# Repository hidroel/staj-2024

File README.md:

# Proje Başlığı: Dizel Motor Su Pompası Ek Modülü

## 1. Giriş
### 1.1 Proje Tanımı
Müşterimiz, tarım sulama sisteminde kullandığı dizel motor su pompası ile ilgili bir sorun yaşamaktadır. Bu proje, bu sorunu tespit etmek ve çözmek amacıyla yürütülecektir.

### 1.2 Amaç ve Hedefler
Projenin amacı, dizel motor su pompasının çalışmasında aksamaya neden olan problemleri belirlemek ve bu problemleri çözmektir. Hedefler:
- Problemin nedenlerini belirlemek
- Çözüm önerileri sunmak
- Çözümün uygulanabilirliğini test etmek
- Nihai çözümü uygulamak

## 2. Mevcut Durum Analizi
### 2.1 Problemin Tanımı
Müşterimiz, dizel su pompası çalışmakta iken su çekilen kanalda suyun kesilmesi sonucunda santifüj'ün susuz kalarak boşta çalıştığını ve yaklaşık 30 saniye sonra yanarak kullanılamaz hale geldiğini belirtmiştir. Su pompasında barometre olmasına rağmen sistemin otomatik olarak durmasını sağlayan bir araç bulunmamaktadır. Başlatma ve durdurma işlemleri tamamen manuel olarak yapılmaktadır. Müşterimiz su kesintisi durumunda sistemin durmasını ve kendisine SMS bilgilendirmesi gelmesini istemektedir.

### 2.2 Önceki Çalışmalar
Konuyla ilgili daha önce herhangi bir modül tasarımı ve uygulaması yapılmamıştır. Yalnızca geçici çözüm olarak müşterimiz su pompasının başında bekleyerek basınç düştüğünde sistemi durdurmaktadır. Bu çözüm iş gücü gerektirmesi ve efektif olmamasından dolayı müşterimiz için kabul edilmemektedir.

## 3. Çözüm Önerileri
### 3.1 Olası Nedenler ve Çözümler
Sorunun nedenleri:
- Su çekilen kanalda belirsiz saatlerde su kesintileri olması.
- Santrifüj'ün boşta çalıştığında fazla sürtünme yapması ve aşırı ısınmasın.
- Su kesintilerinin önceden bildirimi yapılmayıp tamamen plansız olması.

Çözüm Önerileri:
- Su kesintisi önceden biliniyorsa bu saatler aralığında su pompasının çalıştırılmaması.
- Su basıncının entegre bir sistem ile sürekli kontrol edilerek su kesintisi veya azalması durumunda sistemin otomatik olarak kendini durdurması.

### 3.2 Çözümün Uygulanması
En verimli çözüm belirlenmiştir ve çözümün uygulama adımları aşağıdaki gibidir:
1. Su pompası üzerinde bulunan barometre tamamen analog çalıştığı için ek bir basınç sensörü eklenecektir.
2. Basınç sensörü kanaldan gelen hortum üzerinde olacak ve su boşluğu pompaya varmadan önce durumu sisteme bildirebilecektir.
3. Basınç sensöründen uyarı geldiği anda dizel motor durdurulacak ve su çekme işi son bulacaktır.
4. Dizel motorun durdurulabilmesi için yapılacak bağlantı su pompasının aç-kapa anahtarlamasına bağlanacaktır. Su pompası dijital olarak durdurabilecektir.
5. Sistemin durmasının hemen ardından müşteriye SMS iletilecektir.

## 4. Beklenen Sonuçlar ve Ölçümler
### 4.1 Beklenen Sonuçlar
Çözüm yöntemimiz uygulandığında su kesintileri hangi saat aralığında olursa olsun kesinti olduğu anda su pompası otomatik olarak duracak ve sistemin susuz kalmasından dolayı oluşan tüm problemlerden kaçınılacaktır. Ayrıca müşteriye giden SMS sayesinde müşterimiz sistemin durduğunun haberini alarak sulama programını buna göre ayarlayabilecektir.

### 4.2 Başarı Kriterleri

- Su pompasının hiçbir bileşenlerinin susuz kalma sonuçlarından olumsuz etkilenmemesi.
- Müşterinin sulama durduğuna dair bilgiyi eksiksiz ve zamanında alması.

## 5. Zaman Çizelgesi

1. Problemin Analizi: 1 hafta
2. Çözüm Önerilerinin Geliştirilmesi: 1 hafta
3. Çözümün Uygulanması: 2 hafta
4. Test ve Gözlem: 1 hafta
Toplam: 5 hafta

## 6. Kaynaklar ve Bütçe
Projede kullanılacak malzemeler, hizmet ve işçilik maliyeti gibi değişkenler listelenecek ve toplam hesap çıkartılacak.

Tahmini bütçe: HESAPLANACAK

## 7. Kullanılacak Bileşenler

- 1x ADC
- 1x Röle
- 1x MCU (STM32F103RC)
- 1x GSM Modülü (SIM800L HZ-MG2608-C1A-MK-02)
- Yakıt Kesici (UNOX 24V DC Normalde Açık Solenoid Valf)
- 1x Basınç Sensörü (DFRobot SEN0257)
- 3x LED
- 3x Buton

### MCU İçin Gerekli Pinler
- 1x I2C
- 1x SPI
- 4x UART

### Bileşenlerin Kullanım Sebepleri

Proje diyagramında görüldüğü gibi, sistemin çalışma prensibi istenmeyen durum oluştuğunda motorun durdurularak pompanın kapanmasıdır. Kullandığımız basınç sensörü 0-16 bar aralığında olup düzenli ve sık aralıklarla suyun basıncını ölçecektir. Su kesildiğinde hat içerisinde basınç düşecek ve basıncın düşmesi MCU tarafından algılanacak ve valfe bağlı röle tetiklenecektir. Rölenin tetiklenmesi sonucunda normalde açık olan özelliğe sahip valf kapanacak ve dizel motora yakıt akışı duracaktır. Bu sayede dizel motor stop ederek santifüj'ün yanmasını engelleyecektir. MCU röleyi tetiklerken aynı zamanda GSM modülüyle haberleşme sağlayarak müşterimizin telefonuna bildirim SMS'i gitmesini sağlayacaktır.

## 8. Projenin Genel Çalışma Prensibi

Projenin sözel açıklaması şu şekildedir:

MCu'yu barındıran kart ve diğer tüm ek bileşenler dizel motorun aküsünden beslenecektir. Motora ait olan kontak akü ile modüller arasında bağlantıyı sağlamaktadır. Dizel motorun yakıt tankı ile motor arasında bulunan yakıt hortumuna solenoid valf eklenecektir. Bu valf projenin maliyetini düşürmek amacıyla normalde kapalı olarak belirlenmiştir. Solenoid valfin Vin bağlantısı MCU üzerindeki rölenin NC bacağına bağlıdır. Rölenin Common bacağı ise aküden güç almaktadır. Bu sayede, ek modülün herhangi bir sebeple devre dışı kalması durumunda dahi rölede güç akışı devam edecek ve normalde kapalı özelliğe sahip olan valf açık durumda (Yakıt geçişi mümkün) olacaktır.

Projeye özel olarak tasarlanan ek modül kartı, basınç sensörü ile 0-5v protokolü kullanarak analog haberleşme yapacaktır. 2 saniyelik periyotlar ile basınç sensöründen veriler alınarak ADC ile MCU'ya iletilecektir. MCU tarafından basınç kontrol edilerek, istenilen değerin altına düşmesi durumunda röle tetiklenecek ve dizel motor stop ettirilecektir. Bununla eş zamanlı olarak UART ile GSM modülü haberleşmesi sağlanacak ve belirlenen telefon numarasına durumla ilgili SMS gönderilecektir.

Manuel olarak kontak kapatıldığı durumda aküden gelen güç kesildiği için tüm sistem devre dışı kalacaktır. Ayrıca normalde kapalı olan valf herhangi bir tetikleme almadığı için kapalı konuma geçecektir. Bu sayede dizel motor kapalı durumdayken ekstra güvenlik sağlanmış olacaktır.
## 9. Sonuç ve Öneriler
Bu projede belirtilen çözüm adımları doğru bir şekilde uygulandığında ve gerçek uygulama testi analizlerdeki gibi gittiğinde müşterinin tüm sorunu ortadan kaldırılacaktır. Bununla birlikte, sistem uzaktan başlatma ve durdurma gibi ileriye dönük gelişmelere açıktır. Tamamen manuel olarak çalışan su pompası bu entegre ile birlikte durdurma işlemi kontrol edilebilir hale gelmiştir. İleriye dönük eklemeler ve güncellemelerle sistem insan gücünü daha az harcayacak duruma getirilebilir.

Müşteriye eklenen sensörlere ve kartlara zarar vermemesi, afaki koşullarda bulundurmaması için gerekli uyarılar yapılmalıdır. Projede kullanılan akü, kablo gibi zaman içerisinde yıpranan ve ömrünü tüketen materyaller hakkında düzenli bakım yaptırması belirtilmelidir.

Projede kullanılacak kartın diyagrami aşağıdadır:

Projenin çalışma prensibini açıklayan diyagram aşağıdadır:

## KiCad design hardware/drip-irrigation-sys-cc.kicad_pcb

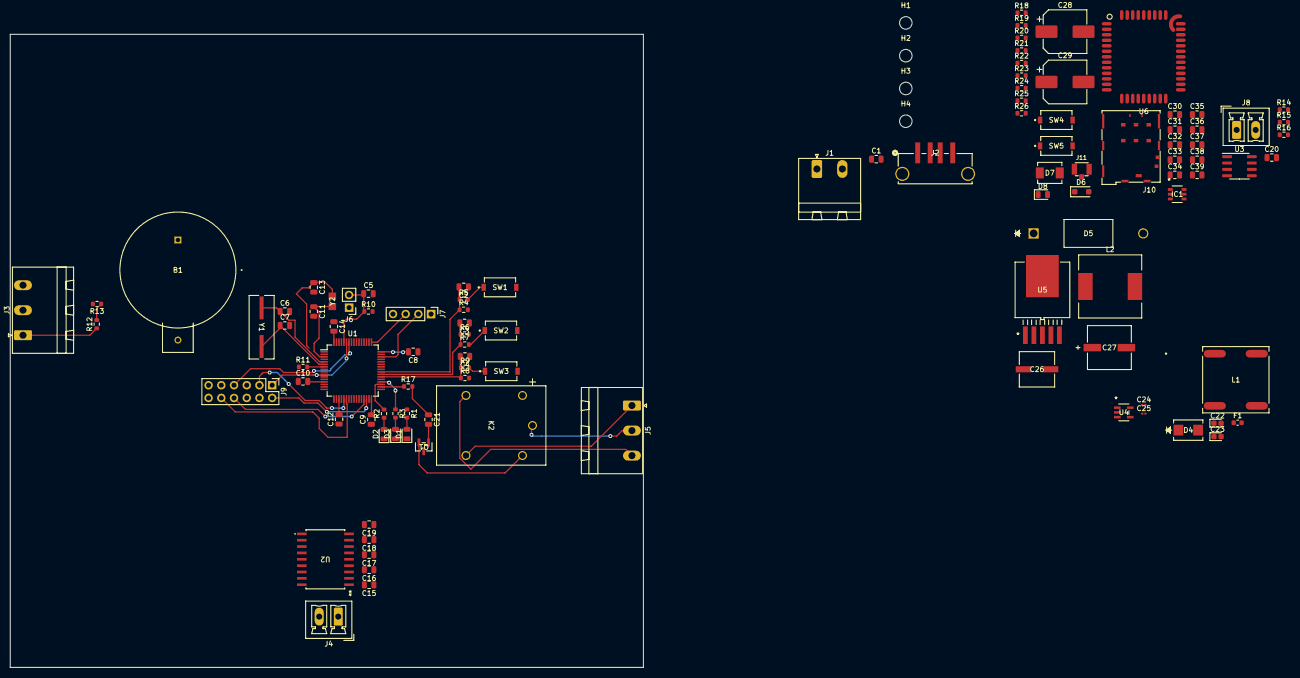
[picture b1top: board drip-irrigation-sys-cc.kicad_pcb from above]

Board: 2 copper layers, 126.5 x 126.5 mm, 108 parts (0 on the bottom side), 81 nets.

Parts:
B1: BH-80B-1; BH-80B-1_ADM
C1, C14: 10nf; C_0805_2012Metric
C2, C3, C4, C5, C8, C9, C10, C12, C21: 100nf; C_0805_2012Metric
C6, C7, C11, C13: 10pf; C_0805_2012Metric
C15, C16, C17, C18, C19, C20: 100nF; C_0805_2012Metric
C22, C23: 33nf; CP_EIA-1608-08_AVX-J
C24, C25: 1uf; C_0201_0603Metric
C26: 100uf; CAP_WCAP-ASLI_06p3X05p5_WRE
C27: 330uf; PCAP_8x10-ELECT_NCA
C28: 100uF; CP_Elec_8x10.5
C29: 470uF; CP_Elec_8x10.5
C30: 100uF; C_0805_2012Metric
C31: 0.1uF; C_0805_2012Metric
C32, C35, C36, C37, C38: 33pF; C_0805_2012Metric
C33, C34: C_0805_2012Metric
C39: 1uF; C_0805_2012Metric
D1: POWER_LED; LED_0805_2012Metric
D2: STATUS_LED; LED_0805_2012Metric
D3: ERROR_LED; LED_0805_2012Metric
D4: D; DIODE_DO214AA_MBRS_VIS
D5: 1N5822; DO-201AD_STM
D6: D; D_SOD-123F
D7: D_Zener; SMB-2_4P60X3P95_ONS
D8: LED; LED_0805_2012Metric
F1: Fuse; Fuse_0603_1608Metric
H1, H2, H3, H4: MountingHole; MountingHole_2.5mm
IC1: DALC208SC6; SOT23-6L_STM
J1: PWR; PhoenixContact_MSTBA_2,5_2-G-5,08_1x02_P5.08mm_Horizontal
J2: USB_A; CONN4X1_UJ2-AV-4-SMT-TR_CUD
J3: PRESSURE_SENSOR; PhoenixContact_MSTBA_2,5_3-G_1x03_P5.00mm_Horizontal
J4, J8: Conn_02x01; PhoenixContact_MCV_1,5_2-G-3.81_1x02_P3.81mm_Vertical
J5: RELAY; PhoenixContact_MSTBA_2,5_3-G_1x03_P5.00mm_Horizontal
J6: Conn_01x02_Pin; PinHeader_1x02_P2.54mm_Vertical
J7: Conn_01x04_Pin; PinHeader_1x04_P2.54mm_Vertical
J9: Conn_02x06_Top_Bottom; PinHeader_2x06_P2.54mm_Vertical
J10: JAE_SIM_Card_SF72S006
J11: U.FL-R-SMT-1_10_; HRS_U.FL-R-SMT-1_10_
K2: G5LE-1 DC5; RELAY_G5LE-1 DC5_OMR
L1: PA2743NL; POLECAT_PA2743NL_PUL
L2: 330uh; L_12x12mm_H8mm
Q1: MMBT3904-TP; SOT-23_MCC
R1, R2, R3: 330ohm; R_0603_1608Metric
R4, R6, R8, R10, R11, R14, R15, R16: 10K; R_0603_1608Metric
R5, R7, R9, R12, R17, R24, R25, R26: 1K; R_0603_1608Metric
R13: 2.74K; R_0603_1608Metric
R18, R19: 0R; R_0603_1608Metric
R20, R21, R22: 22R; R_0603_1608Metric
R23: 15K; R_0603_1608Metric
SW1, SW4, SW5: BTN_DEACTIVE; SW_PTS636_CNK
SW2: BTN_IO; SW_PTS636_CNK
SW3: BTN_ACTIVE; SW_PTS636_CNK
U1: STM32F103RCTx; LQFP-64_10x10mm_P0.5mm
U2: MAX3222EWN_T; MAX3222EWN+T
U3: Max3075EESA; SOIC-8_3.9x4.9mm_P1.27mm
U4: MIC5504-3.3YM5-TR
U5: LM2576-5.0WU-TR
U6: MG2608
Y1: 8MHZ; XTAL_ABLS2_ABR
Y2: 32KHZ; XTAL_CM7V-T1A_MCX

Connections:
+3.3V: C8.2, C9.2, C10.2, C12.2, C14.2, C25.1, J6.1, J9.4, J9.5, R11.1, U1.13 (VDDA), U1.19 (VDD), U1.32 (VDD), U1.48 (VDD), U1.64 (VDD), U4.5 (VOUT)
+3V3: C19.1, C20.1, R15.1, U2.17 (VCC), U2.18 (~SHDN), U3.8 (VCC)
+5V: C24.1, C27.1, D6.2 (A), J2.1 (VBUS), J3.2, J7.1, J9.6, L2.2, Q1.3, R1.1, R4.2, R6.2, R8.2, R14.1, U3.2 (~RE), U3.3 (DE), U4.1 (VIN), U4.3 (EN), U5.4 (FEEDBACK)
+12V: C23.1, C26.1, L1.3, U5.1 (VIN)
/ADC/MCU_ADC: R12.2, R13.1, U1.14 (PA0)
/ADC/PRESSURE_SENSOR_ANALOG_SIGNAL: J3.1, R12.1
/EXP/I2C_SDA: J9.1, U1.59 (PB7)
/EXP/I2C_SDL: J9.7, U1.58 (PB6)
/EXP/SPI_MISO: J9.10, U1.22 (PA6)
/EXP/SPI_MOSI: J9.9, U1.23 (PA7)
/EXP/SPI_SCK: J9.3, U1.21 (PA5)
/EXP/USAR3_RX: J9.2, U1.30 (PB11)
/EXP/USART3_TX: J9.8, U1.29 (PB10)
/GSM_Module/4v: C28.1, C29.1, C30.1, C31.1, C32.1, D6.1 (K), D7.1 (K), R23.1, U6.42 (VBAT), U6.43 (VBAT)
/GSM_Module/PWRKEY: R26.1, U6.7 (PWRKEY)
/GSM_Module/REST: R25.1, U6.26 (REST)
/GSM_Module/RF_ANT: R18.2, U6.35 (RF_ANT)
/GSM_Module/SIM_CLK: C36.1, IC1.3 (I/O_2), R21.2, U6.13 (SIM_CLK)
/GSM_Module/SIM_DATA: C35.1, IC1.1 (I/O_1), R22.2, R23.2, U6.11 (SIM_DATA)
/GSM_Module/SIM_RST: C37.1, IC1.4 (I/O_3), R20.2, U6.12 (SIM_RST)
/GSM_Module/SIM_VDD: C38.1, C39.1, IC1.6 (I/O_4), J10.C1 (VCC), U6.14 (SIM_VDD)
/GSM_Module/UART_RX: U1.52 (PC11), U6.17 (UART1_RXD)
/GSM_Module/UART_TX: U1.51 (PC10), U6.18 (UART1_TXD)
/MCU/BOOT0: C5.1, J6.2, R10.1, U1.60 (BOOT0)
/MCU/BTN_ACTIVATE: C3.2, R6.1, R7.1, U1.39 (PC8)
/MCU/BTN_DEACTIVATE: C2.2, R4.1, R5.1, U1.40 (PC9)
/MCU/BTN_IO: C4.2, R8.1, R9.1, U1.38 (PC7)
/MCU/MCU_ERROR_LED: R3.1, U1.36 (PB15)
/MCU/MCU_RELAY: R17.1, U1.34 (PB13)
/MCU/MCU_STATUS_LED: R2.2, U1.35 (PB14)
/MCU/USAR1_RX: U1.43 (PA10), U2.13 (R1OUT)
/MCU/USART1_TX: U1.42 (PA9), U2.12 (T1IN)
/MCU/USART2_RX: U1.17 (PA3), U3.1 (RO)
/MCU/USART2_TX: U1.16 (PA2), U3.4 (DI)
/MCU/USB_DM: J2.2 (D-), U1.44 (PA11)
/MCU/USB_DP: J2.3 (D+), U1.45 (PA12)
/Power/PWR_GND: C22.2, J1.2, L1.2
/Power/PWR_VCC: F1.1, J1.1
/RS-232/RS232_RX: J4.1, U2.14 (R1IN)
/RS-232/RS232_TX: J4.2, U2.15 (T1OUT)
/Relay/COM: J5.2, K2.1
/Relay/NC: J5.1, K2.4
/Relay/NO: J5.3, K2.3
GND: B1.1, C1.2, C2.1, C3.1, C4.1, C5.2, C6.2, C7.2, C8.1, C9.1, C10.1, C11.2, C12.1, C13.2, C14.1, C17.2, C18.2, C19.2, C20.2, C23.2, C24.2, C25.2, C26.2, C27.2, C28.2, C29.2, C30.2, C31.2, C32.2, C33.2, C34.2, C35.2, C36.2, C37.2, C38.2, C39.2, D1.1 (K), D2.1 (K), D3.1 (K), D5.2 (A), D7.2 (A), D8.1 (K), IC1.5 (REF_1), J2.4 (GND), J3.3, J7.4, J9.11, J9.12, J10.C5 (GND), J11.1, K2.2, L1.4, R10.2, R13.2, R14.2, R16.2, SW1.2, SW2.2, SW3.2, SW4.2, SW5.2, U1.12 (VSSA), U1.18 (VSS), U1.31 (VSS), U1.47 (VSS), U1.63 (VSS), U2.1 (~EN), U2.16 (GND), U3.5 (GND), U4.2 (GND), U5.3 (GROUND), U5.5 (*ON/OFF), U6.1 (GND), U6.10 (GND), U6.27 (GND), U6.34 (GND), U6.36 (GND), U6.37 (GND), U6.40 (GND), U6.41 (GND)
unnamed: C21.1, R17.2
unnamed: C21.2, Q1.1
unnamed: C33.1, R18.1, R19.2
unnamed: C34.1, J11.2, R19.1
unnamed: D1.2 (A), R1.2
unnamed: D2.2 (A), R2.1
unnamed: D3.2 (A), R3.2
unnamed: D4.2 (A), F1.2
unnamed: C22.1, D4.1 (K), L1.1
unnamed: D5.1 (K), L2.1, U5.2 (OUTPUT)
unnamed: D8.2 (A), R24.2
unnamed: C1.1, J2.5 (Shield)
unnamed: J7.2, U1.46 (PA13)
unnamed: J7.3, U1.49 (PA14)
unnamed: J8.1, R15.2, U3.6 (A)
unnamed: J8.2, R16.1, U3.7 (B)
unnamed: J10.C3 (CLK), R21.1
unnamed: J10.C7 (I/O), R22.1
unnamed: J10.C2 (RST), R20.1
unnamed: K2.5, Q1.2
unnamed: R5.2, SW1.1
unnamed: R7.2, SW2.1
unnamed: R9.2, SW3.1
unnamed: R25.2, SW4.1
unnamed: R26.2, SW5.1
unnamed: R11.2, U1.7 (NRST)
unnamed: C11.1, U1.3 (PC14), Y2.1
unnamed: C13.1, U1.4 (PC15), Y2.2
unnamed: C6.1, U1.5 (PD0), Y1.1
unnamed: C7.1, U1.6 (PD1), Y1.2
unnamed: B1.2, U1.1 (VBAT)
unnamed: C16.1, U2.2 (C1+)
unnamed: C16.2, U2.4 (C1-)
unnamed: C15.1, U2.5 (C2+)
unnamed: C15.2, U2.6 (C2-)
unnamed: C18.1, U2.3 (V+)
unnamed: C17.1, U2.7 (V-)

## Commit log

2024-08-07 Proje dizinleri duzenlendi.
2024-08-07 Diagram ornegi eklendi
2024-08-07 Diyagramlar güncellendi.
2024-08-07 README.md düzenlendi.
2024-08-08 Diyagramlar ve dökümanlar düzenlendi.
2024-08-08 Yeni diyagram eklendi ve serial.md düzenlendi.
2024-08-08 serial.md mini düzenleme yapıldı.
2024-08-08 KiCad projesi olusturuldu.
2024-08-09 README.md, analog.md, serial.md dosyaları düzenlendi.
2024-08-11 analog.md düzenlendi, 1 adet diyagram ve 2 adet görsel eklendi.
2024-08-11 analog.md mini düzenleme yapıldı.
2024-08-11 analog.md yazım hataları düzeltildi.
2024-08-12 Yeni resimler ve diyagramlar eklendi. relay_leds_usage.md dosyası oluşturuldu.
2024-08-12 relay_leds_usage.md dosyası relay_leds_buttons_usage.md olarak düzenlendi. İçeriğinde değişiklikler yapıldı.
2024-08-13 Diyagramlarda kelime düzenlemesi yapıldı.
2024-08-15 power.md düzenlendi. Yeni görseller eklendi.
2024-08-18 power.kicad_sch düzenlemesi yapıldı.
2024-08-22 Kicad şema düzenlemesi yapıldı.
2024-08-27 Kicad Power Modülü Tamamlandı.
2024-09-03 Kicad düzenleme.
2024-09-12 Kicad şema düzenlemesi.
2024-09-12 Kicad PCB düzenlemesi yapıldı.
2024-09-18 PCB düzenlemesi yapıldı.
2024-10-01 PCB düzenlemesi.
2024-10-01 PCB düzenleme.
